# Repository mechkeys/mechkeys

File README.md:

# mechkeys

A few mechanical keyboard related kicad projects.

[103-key](http://www.keyboard-layout-editor.com/##@@=PrtSc&=Scroll%20Lock&=Pause%0ABreak&_x:1.25%3B&=Esc&_x:1%3B&=F1&=F2&=F3&=F4&_x:0.5%3B&=F5&=F6&=F7&=F8&_x:0.5%3B&=F9&=F10&=F11&=F12&_x:0.25&a:7%3B&=Home&=End%3B&@_y:0.5%3B&=Num%20Lock&=%2F%2F&=*&=-&_x:0.25&a:4%3B&=%7E%0A%60&=!%0A1&=%2F@%0A2&=%23%0A3&=$%0A4&=%25%0A5&=%5E%0A6&=%2F&%0A7&=*%0A8&=%28%0A9&=%29%0A0&=%2F_%0A-&=+%0A%2F=&_w:2%3B&=Backspace&_x:0.25&a:7%3B&=Ins&=PgUp%3B&@_f:3%3B&=7%0AHome&=8%0A%E2%86%91&=9%0APgUp&_h:2%3B&=+&_x:0.25&a:4&w:1.5%3B&=Tab&=Q&=W&=E&=R&=T&=Y&=U&=I&=O&=P&=%7B&=%7D&_w:1.5%3B&=%7C&_x:0.25%3B&=Del&=PgDn%3B&@=4%0A%E2%86%90&=5&=6%0A%E2%86%92&_x:1.25&a:4&w:1.75%3B&=Caps%20Lock&=A&=S&=D&=F&=G&=H&=J&=K&=L&=%2F:&=%22&_w:2.25%3B&=Enter%3B&@=1%0AEnd&=2%0A%E2%86%93&=3%0APgDn&_h:2%3B&=Enter&_x:0.25&a:4&w:2.25%3B&=Shift&=Z&=X&=C&=V&=B&=N&=M&=%3C&=%3E&=%3F&_w:2.75%3B&=Shift&_x:0.25%3B&=%E2%86%91%3B&@_w:2%3B&=0%0AIns&=.%0ADel&_x:1.25&a:4&w:1.25%3B&=Ctrl&_w:1.25%3B&=Win&_w:1.25%3B&=Alt&_w:6.25%3B&=&_a:4&w:1.25%3B&=Alt&_w:1.25%3B&=Win&_w:1.25%3B&=Menu&_x:0.5&a:7%3B&=%E2%86%90&=%E2%86%93&=%E2%86%92): A layout from w00dyallen in this post: [my_dream_layout_103key_99](https://www.reddit.com/r/MechanicalKeyboards/comments/4l9j7y/my_dream_layout_103key_99/)

layout.py: python script that will layout out a pcb and schematic from the output of http://www.keyboard-layout-editor.com/

dylibfix.sh: shell script that will fix the lib security errors in osx.

Apologies- I had to wipe the original and replace it. The new repo does not have most of my kicad projects. If you want a copy send me a message, but I can't keep them in the open any more.

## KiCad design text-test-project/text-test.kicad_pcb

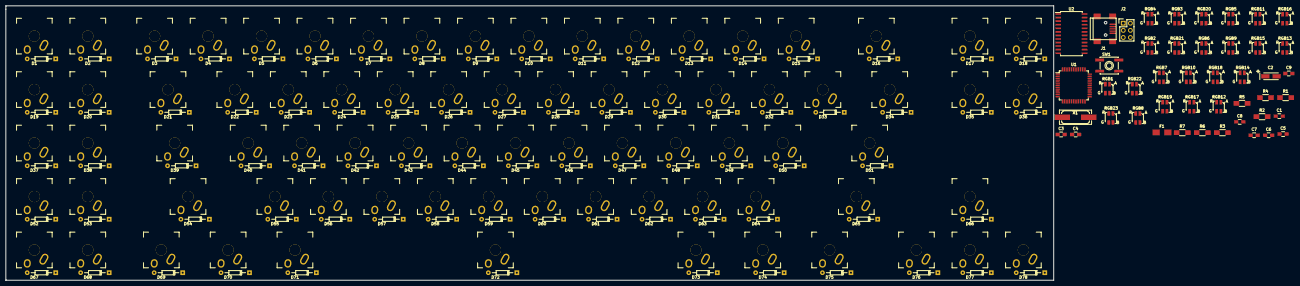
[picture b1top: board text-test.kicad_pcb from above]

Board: 2 copper layers, 373.4 x 97.8 mm, 202 parts (0 on the bottom side), 133 nets, no tracks yet.

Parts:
C1: C; C_0805_HandSoldering
C2: 10µF; TantalC_SizeA_EIA-3216_HandSoldering
C3, C4, C5, C9: 0.1µF; C_0805_HandSoldering
C6, C7: 18pF; C_0805_HandSoldering
C8: 1µF; C_0805_HandSoldering
D1, D2, D3, D4, D5, D6, D7, D8, D9, D10, D11, D12, D13, D14, D15, D16, D17, D18, D19, D20, D21, D22, D23, D24, D25, D26, D27, D28, D29, D30, D31, D32, D33, D34, D35, D36, D37, D38, D39, D40, D41, D42, D43, D44, D45, D46, D47, D48, D49, D50, D51, D52, D53, D54, D55, D56, D57, D58, D59, D60, D61, D62, D63, D64, D65, D66, D67, D68, D69, D70, D71, D72, D73, D74, D75, D76, D77, D78: D; Diode_DO-35_SOD27_Horizontal_RM10
F1: FP_Small; Fuse_SMD1206_HandSoldering
J1: USB_OTG; USB_Mini-B
J2: PRG; Pin_Header_Straight_2x03
R1: R; R_1206_HandSoldering
R2: R2; R_1206_HandSoldering
R3: R3; R_1206_HandSoldering
R4: R4; R_1206_HandSoldering
R5, R6: 22; R_1206_HandSoldering
R7: 10k; R_1206_HandSoldering
RGB1, RGB2, RGB3, RGB4, RGB5, RGB6, RGB7, RGB8, RGB9, RGB10, RGB11, RGB12, RGB13, RGB14, RGB15, RGB16, RGB17, RGB18, RGB19, RGB20, RGB21, RGB22, RGB23: Led_RGB_CA; SMP4-RGB
SW1: SW_RST; SW_SPST_EVQP0
SW_A_40: MX_LED; MXALPS-NOLED
SW_Alt_71, SW_Alt_73: MX_LED; MXALPS-NOLED
SW_B_59: MX_LED; MXALPS-NOLED
SW_Backspace_16: MX_LED; MXALPS-NOLED
SW_C_57: MX_LED; MXALPS-NOLED
SW_Caps_39: MX_LED; MXALPS-NOLED
SW_Ctrl_69: MX_LED; MXALPS-NOLED
SW_D_42: MX_LED; MXALPS-NOLED
SW_Del_35: MX_LED; MXALPS-NOLED
SW_E_24: MX_LED; MXALPS-NOLED
SW_Enter_51: MX_LED; MXALPS-NOLED
SW_F1_1, SW_F2_2, SW_F3_19, SW_F4_20, SW_F5_37, SW_F6_38, SW_F7_52, SW_F8_53, SW_F9_67, SW_F10_68: MX_LED; MXALPS-NOLED
SW_F_43: MX_LED; MXALPS-NOLED
SW_G_44: MX_LED; MXALPS-NOLED
SW_H_45: MX_LED; MXALPS-NOLED
SW_I_29: MX_LED; MXALPS-NOLED
SW_Ins_17: MX_LED; MXALPS-NOLED
SW_J_46: MX_LED; MXALPS-NOLED
SW_K_47: MX_LED; MXALPS-NOLED
SW_L_48: MX_LED; MXALPS-NOLED
SW_M_61: MX_LED; MXALPS-NOLED
SW_Menu_75: MX_LED; MXALPS-NOLED
SW_N_60: MX_LED; MXALPS-NOLED
SW_O_30: MX_LED; MXALPS-NOLED
SW_P_31: MX_LED; MXALPS-NOLED
SW_PgDn_36: MX_LED; MXALPS-NOLED
SW_PgUp_18: MX_LED; MXALPS-NOLED
SW_Q_22: MX_LED; MXALPS-NOLED
SW_R_25: MX_LED; MXALPS-NOLED
SW_S_41: MX_LED; MXALPS-NOLED
SW_Shift_54, SW_Shift_65: MX_LED; MXALPS-NOLED
SW_T_26: MX_LED; MXALPS-NOLED
SW_Tab_21: MX_LED; MXALPS-NOLED
SW_U_28: MX_LED; MXALPS-NOLED
SW_V_58: MX_LED; MXALPS-NOLED
SW_W_23: MX_LED; MXALPS-NOLED
SW_Win_70, SW_Win_74: MX_LED; MXALPS-NOLED
SW_X4Y1_3, SW_X5Y1_4, SW_X6Y1_5, SW_X7Y1_6, SW_X8Y1_7, SW_X8Y5_72, SW_X9Y1_8, SW_X10Y1_9, SW_X11Y1_10, SW_X12Y1_11, SW_X13Y1_12, SW_X13Y4_62, SW_X14Y1_13, SW_X14Y4_63, SW_X15Y1_14, SW_X15Y2_32, SW_X15Y3_49, SW_X15Y4_64, SW_X16Y1_15, SW_X16Y2_33, SW_X16Y3_50, SW_X17Y2_34, SW_X18Y5_76, SW_X19Y4_66, SW_X19Y5_77, SW_X20Y5_78: MX_LED; MXALPS-NOLED
SW_X_56: MX_LED; MXALPS-NOLED
SW_Y_27: MX_LED; MXALPS-NOLED
SW_Z_55: MX_LED; MXALPS-NOLED
U1: ATMEGA32U4RC-A; TQFP-44_10x10mm_Pitch0.8mm
U2: AN32183A; SOIC-24_7.5x15.4mm_Pitch1.27mm
X1: 16Mhz; Q_49U3HMS

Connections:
+5V: C2.1, C3.1, C4.1, C5.1, F1.2, J2.2, R7.2, RGB1.1, U1.2, U1.7, U1.14, U1.24, U1.34, U1.44
C1: SW_F1_1.SW1, SW_F3_19.SW1, SW_F5_37.SW1, SW_F7_52.SW1, SW_F9_67.SW1, SW_H_45.SW1, SW_Menu_75.SW1, SW_N_60.SW1, SW_X10Y1_9.SW1, SW_Y_27.SW1, U1.31
C2: SW_F2_2.SW1, SW_F4_20.SW1, SW_F6_38.SW1, SW_F8_53.SW1, SW_F10_68.SW1, SW_J_46.SW1, SW_M_61.SW1, SW_U_28.SW1, SW_X11Y1_10.SW1, SW_X18Y5_76.SW1, U1.32
C3: SW_Caps_39.SW1, SW_Ctrl_69.SW1, SW_I_29.SW1, SW_K_47.SW1, SW_Shift_54.SW1, SW_Tab_21.SW1, SW_X4Y1_3.SW1, SW_X12Y1_11.SW1, SW_X13Y4_62.SW1, SW_X19Y5_77.SW1
C4: SW_A_40.SW1, SW_L_48.SW1, SW_O_30.SW1, SW_Q_22.SW1, SW_Win_70.SW1, SW_X5Y1_4.SW1, SW_X13Y1_12.SW1, SW_X14Y4_63.SW1, SW_X20Y5_78.SW1, SW_Z_55.SW1
C5: SW_Alt_71.SW1, SW_Ins_17.SW1, SW_P_31.SW1, SW_S_41.SW1, SW_W_23.SW1, SW_X6Y1_5.SW1, SW_X14Y1_13.SW1, SW_X15Y3_49.SW1, SW_X15Y4_64.SW1, SW_X_56.SW1
C6: SW_C_57.SW1, SW_D_42.SW1, SW_E_24.SW1, SW_PgUp_18.SW1, SW_Shift_65.SW1, SW_X7Y1_6.SW1, SW_X8Y5_72.SW1, SW_X15Y1_14.SW1, SW_X15Y2_32.SW1, SW_X16Y3_50.SW1
C7: SW_Alt_73.SW1, SW_Del_35.SW1, SW_Enter_51.SW1, SW_F_43.SW1, SW_R_25.SW1, SW_V_58.SW1, SW_X8Y1_7.SW1, SW_X16Y1_15.SW1, SW_X16Y2_33.SW1, SW_X19Y4_66.SW1
C8: SW_B_59.SW1, SW_Backspace_16.SW1, SW_G_44.SW1, SW_PgDn_36.SW1, SW_T_26.SW1, SW_Win_74.SW1, SW_X9Y1_8.SW1, SW_X17Y2_34.SW1
D+: R6.1, U1.4
D-: R5.1, U1.3
GND: C1.2, C2.2, C3.2, C4.2, C5.2, C6.2, C7.2, C8.2, C9.2, J1.5, J1.6, J2.6, R1.2, SW1.1, U1.5, U1.15, U1.23, U1.33, U1.35, U1.43, U2.4, U2.9, U2.15, U2.23
LED_NSRT: U1.36, U2.22
LED_SCL: U1.18, U2.2
LED_SDA: U1.19, U2.3
unnamed: C1.1, U2.1, U2.13
unnamed: C6.1, U1.17, X1.1
unnamed: C7.1, U1.16, X1.2
unnamed: C8.1, U1.6
unnamed: C9.1, U1.42
unnamed: D1.2, SW_F1_1.SW2
unnamed: D2.2, SW_F2_2.SW2
unnamed: D3.2, SW_X4Y1_3.SW2
unnamed: D4.2, SW_X5Y1_4.SW2
unnamed: D5.2, SW_X6Y1_5.SW2
unnamed: D6.2, SW_X7Y1_6.SW2
unnamed: D7.2, SW_X8Y1_7.SW2
unnamed: D8.2, SW_X9Y1_8.SW2
unnamed: D9.2, SW_X10Y1_9.SW2
unnamed: D10.2, SW_X11Y1_10.SW2
unnamed: D11.2, SW_X12Y1_11.SW2
unnamed: D12.2, SW_X13Y1_12.SW2
unnamed: D13.2, SW_X14Y1_13.SW2
unnamed: D14.2, SW_X15Y1_14.SW2
unnamed: D15.2, SW_X16Y1_15.SW2
unnamed: D16.2, SW_Backspace_16.SW2
unnamed: D17.1, D18.1, D35.1, D36.1, D78.2, SW_X20Y5_78.SW2
unnamed: D17.2, SW_Ins_17.SW2
unnamed: D18.2, SW_PgUp_18.SW2
unnamed: D19.1, D20.1, D21.1, D22.1, D23.1, D24.1, D25.1, D26.1
unnamed: D19.2, SW_F3_19.SW2
unnamed: D20.2, SW_F4_20.SW2
unnamed: D21.2, SW_Tab_21.SW2
unnamed: D22.2, SW_Q_22.SW2
unnamed: D23.2, SW_W_23.SW2
unnamed: D24.2, SW_E_24.SW2
unnamed: D25.2, SW_R_25.SW2
unnamed: D26.2, SW_T_26.SW2
unnamed: D27.2, SW_Y_27.SW2
unnamed: D28.2, SW_U_28.SW2
unnamed: D29.2, SW_I_29.SW2
unnamed: D30.2, SW_O_30.SW2
unnamed: D31.2, SW_P_31.SW2
unnamed: D32.2, SW_X15Y2_32.SW2
unnamed: D33.2, SW_X16Y2_33.SW2
unnamed: D34.2, SW_X17Y2_34.SW2
unnamed: D35.2, SW_Del_35.SW2
unnamed: D36.2, SW_PgDn_36.SW2
unnamed: D37.1, D38.1, D39.1, D40.1, D41.1, D42.1, D43.1, D44.1
unnamed: D37.2, SW_F5_37.SW2
unnamed: D38.2, SW_F6_38.SW2
unnamed: D39.2, SW_Caps_39.SW2
unnamed: D40.2, SW_A_40.SW2
unnamed: D41.2, SW_S_41.SW2
unnamed: D42.2, SW_D_42.SW2
unnamed: D43.2, SW_F_43.SW2
unnamed: D44.2, SW_G_44.SW2
unnamed: D45.2, SW_H_45.SW2
unnamed: D46.2, SW_J_46.SW2
unnamed: D47.2, SW_K_47.SW2
unnamed: D48.2, SW_L_48.SW2
unnamed: D49.2, SW_X15Y3_49.SW2
unnamed: D50.2, SW_X16Y3_50.SW2
unnamed: D51.2, SW_Enter_51.SW2
unnamed: D52.1, D53.1, D54.1, D55.1, D56.1, D57.1, D58.1, D59.1
unnamed: D52.2, SW_F7_52.SW2
unnamed: D53.2, SW_F8_53.SW2
unnamed: D54.2, SW_Shift_54.SW2
unnamed: D55.2, SW_Z_55.SW2
unnamed: D56.2, SW_X_56.SW2
unnamed: D57.2, SW_C_57.SW2
unnamed: D58.2, SW_V_58.SW2
unnamed: D59.2, SW_B_59.SW2
unnamed: D60.2, SW_N_60.SW2
unnamed: D61.2, SW_M_61.SW2
unnamed: D62.2, SW_X13Y4_62.SW2
unnamed: D63.2, SW_X14Y4_63.SW2
unnamed: D64.2, SW_X15Y4_64.SW2
unnamed: D65.2, SW_Shift_65.SW2
unnamed: D66.2, SW_X19Y4_66.SW2
unnamed: D67.2, SW_F9_67.SW2
unnamed: D68.2, SW_F10_68.SW2
unnamed: D69.2, SW_Ctrl_69.SW2
unnamed: D70.2, SW_Win_70.SW2
unnamed: D71.2, SW_Alt_71.SW2
unnamed: D72.2, SW_X8Y5_72.SW2
unnamed: D73.2, SW_Alt_73.SW2
unnamed: D74.2, SW_Win_74.SW2
unnamed: D75.2, SW_Menu_75.SW2
unnamed: D76.2, SW_X18Y5_76.SW2
unnamed: D77.2, SW_X19Y5_77.SW2
unnamed: F1.1, J1.1
unnamed: J1.2, R5.2
unnamed: J1.3, R6.2
unnamed: R1.1, U2.24
unnamed: R2.1, RGB1.4
unnamed: R3.1, RGB1.3
unnamed: R4.1, RGB1.2
unnamed: U2.7, U2.17
PWM_BLUE: R2.2, U1.12
PWM_GREEN: R3.2, U1.30
PWM_RED: R4.2, U1.29
R1: D1.1, D2.1, D3.1, D4.1, D5.1, D6.1, D7.1, D8.1, U1.8
R2/SCK: J2.3, U1.9
R3/MOSI: J2.4, U1.10
R4/MISO: J2.1, U1.11
R5: D67.1, D68.1, D69.1, D70.1, D71.1, D72.1, D73.1, D74.1, U1.28
R6: D9.1, D10.1, D11.1, D12.1, D13.1, D14.1, D15.1, D16.1, U1.41
R7: D27.1, D28.1, D29.1, D30.1, D31.1, D32.1, D33.1, D34.1, U1.40
R8: D45.1, D46.1, D47.1, D48.1, D49.1, D50.1, D51.1, U1.39
R9: D60.1, D61.1, D62.1, D63.1, D64.1, D65.1, D66.1, U1.38
R10: D75.1, D76.1, D77.1, D78.1, U1.37
RST: J2.5, R7.1, SW1.2, U1.13
Z1: RGB2.3, RGB3.1, RGB5.1, RGB13.1, RGB22.3, RGB23.3, U2.19
Z2: RGB2.2, RGB3.2, RGB6.1, RGB9.2, RGB10.2, RGB11.2, RGB12.2, RGB14.1, U2.18
Z3: RGB2.1, RGB3.3, RGB7.1, RGB9.3, RGB10.3, RGB11.3, RGB12.3, RGB15.1, U2.16
Z4: RGB2.4, RGB3.4, RGB4.4, RGB8.1, RGB9.4, RGB10.4, RGB11.4, RGB12.4, RGB16.1, U2.14
Z5: RGB4.2, RGB5.2, RGB6.2, RGB7.2, RGB8.2, RGB9.1, RGB17.1, RGB20.2, RGB21.2, RGB22.2, U2.12
Z6: RGB4.3, RGB5.3, RGB6.3, RGB7.3, RGB8.3, RGB10.1, RGB18.1, RGB20.3, RGB21.3, RGB22.1, U2.11
Z7: RGB4.1, RGB5.4, RGB6.4, RGB7.4, RGB8.4, RGB19.1, RGB20.4, RGB21.4, RGB22.4, U2.10
Z8: RGB11.1, RGB13.2, RGB14.2, RGB15.2, RGB16.2, RGB17.2, RGB18.2, RGB19.2, RGB20.1, RGB23.2, U2.8
Z9: RGB12.1, RGB13.3, RGB14.3, RGB15.3, RGB16.3, RGB17.3, RGB18.3, RGB19.3, RGB21.1, RGB23.1, U2.6
Z10: RGB13.4, RGB14.4, RGB15.4, RGB16.4, RGB17.4, RGB19.4, RGB23.4, U2.5

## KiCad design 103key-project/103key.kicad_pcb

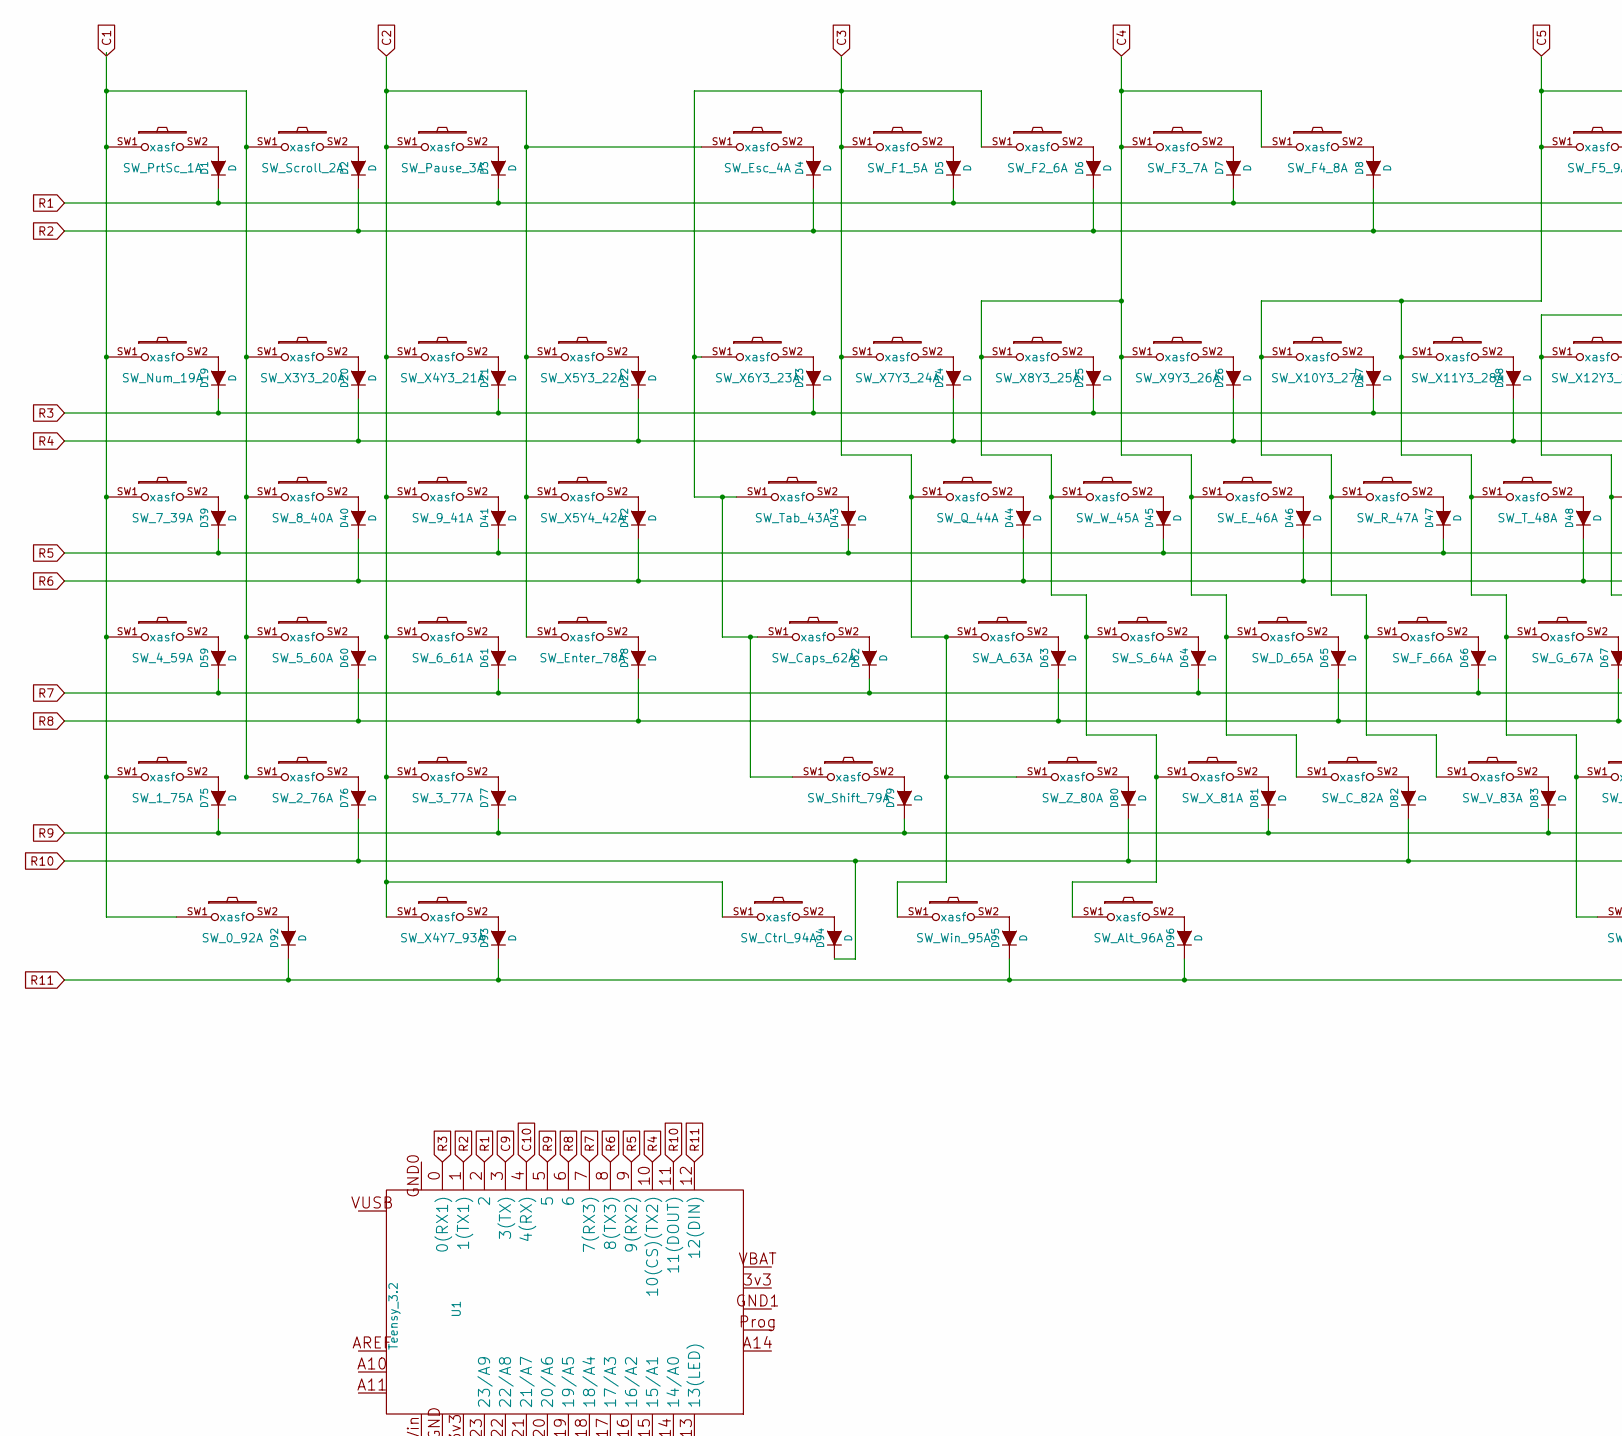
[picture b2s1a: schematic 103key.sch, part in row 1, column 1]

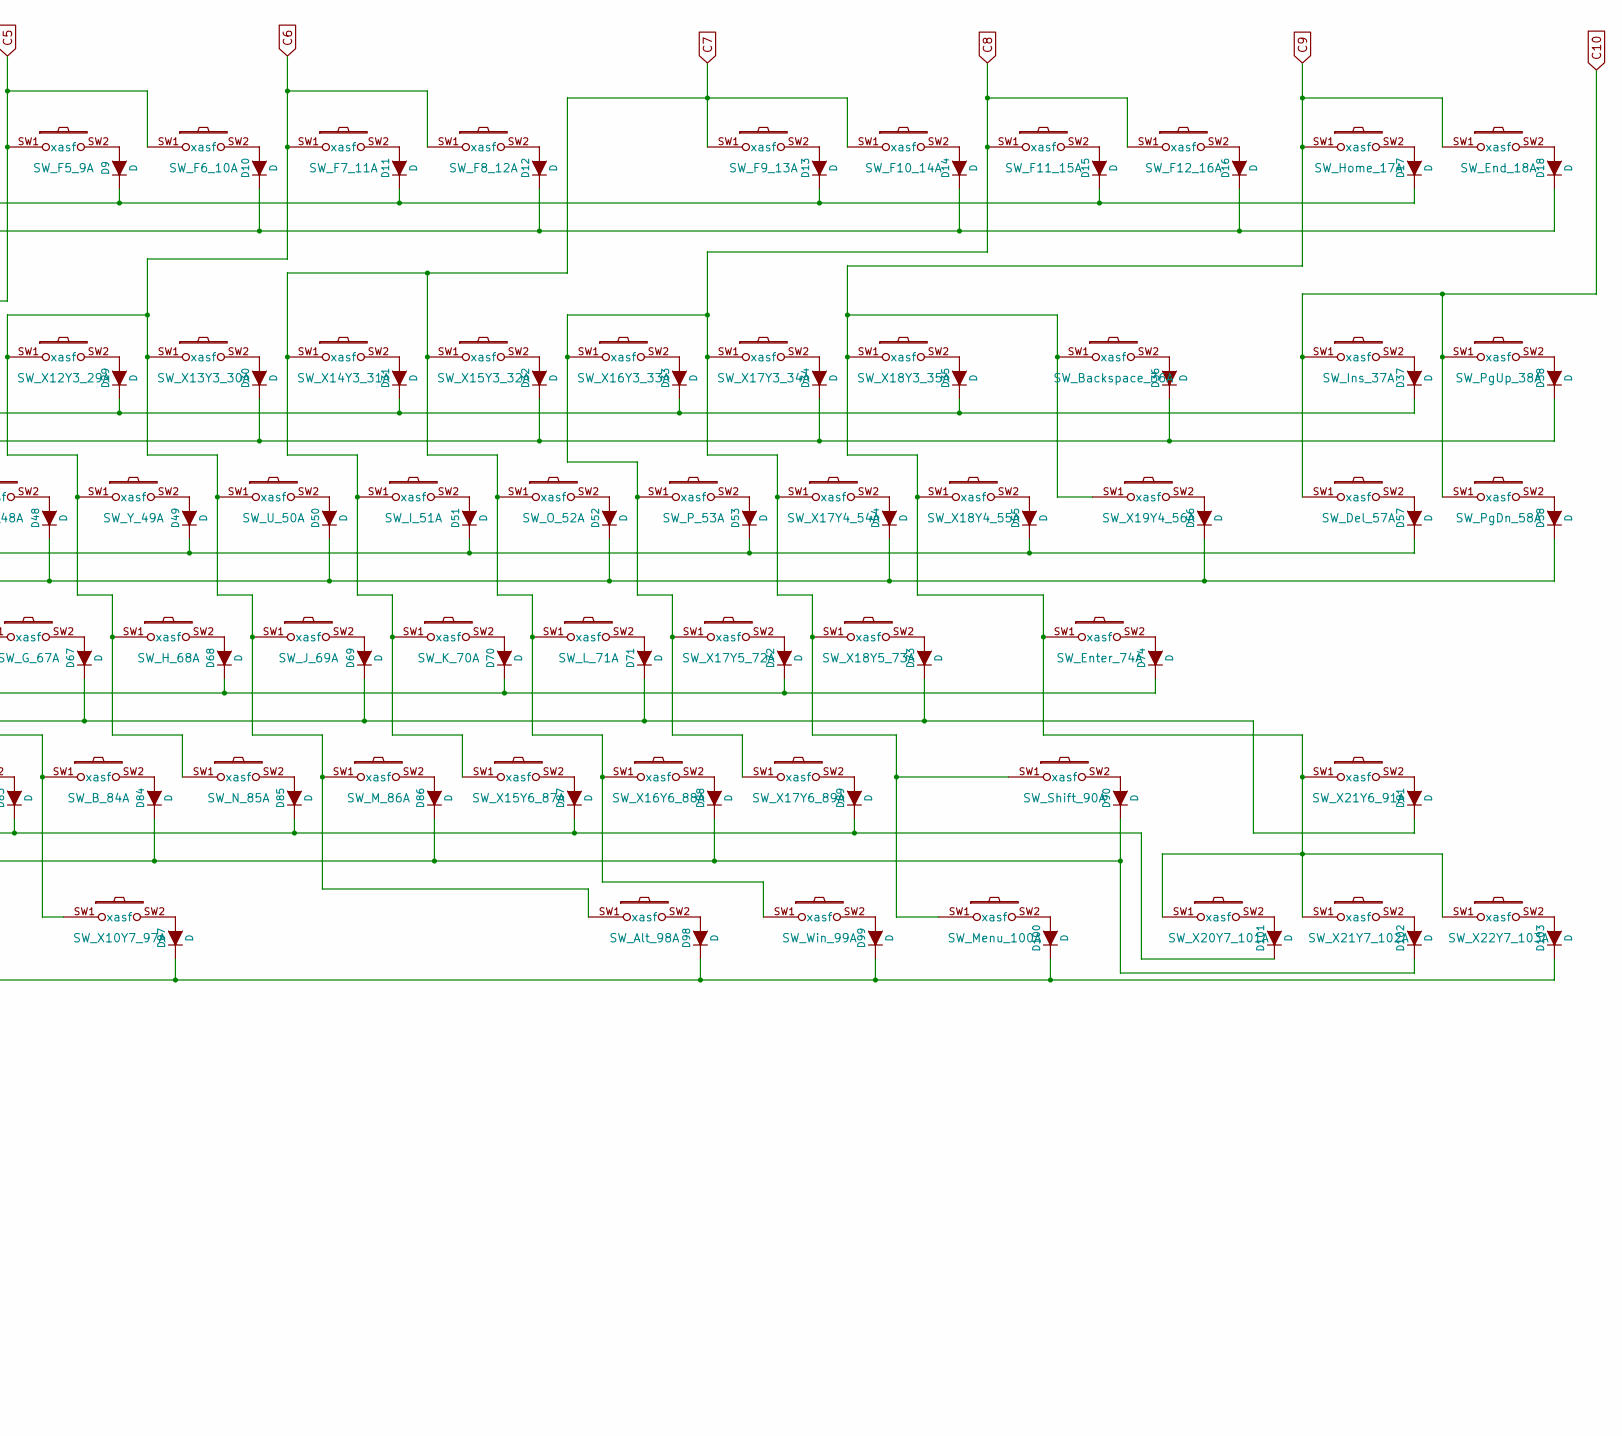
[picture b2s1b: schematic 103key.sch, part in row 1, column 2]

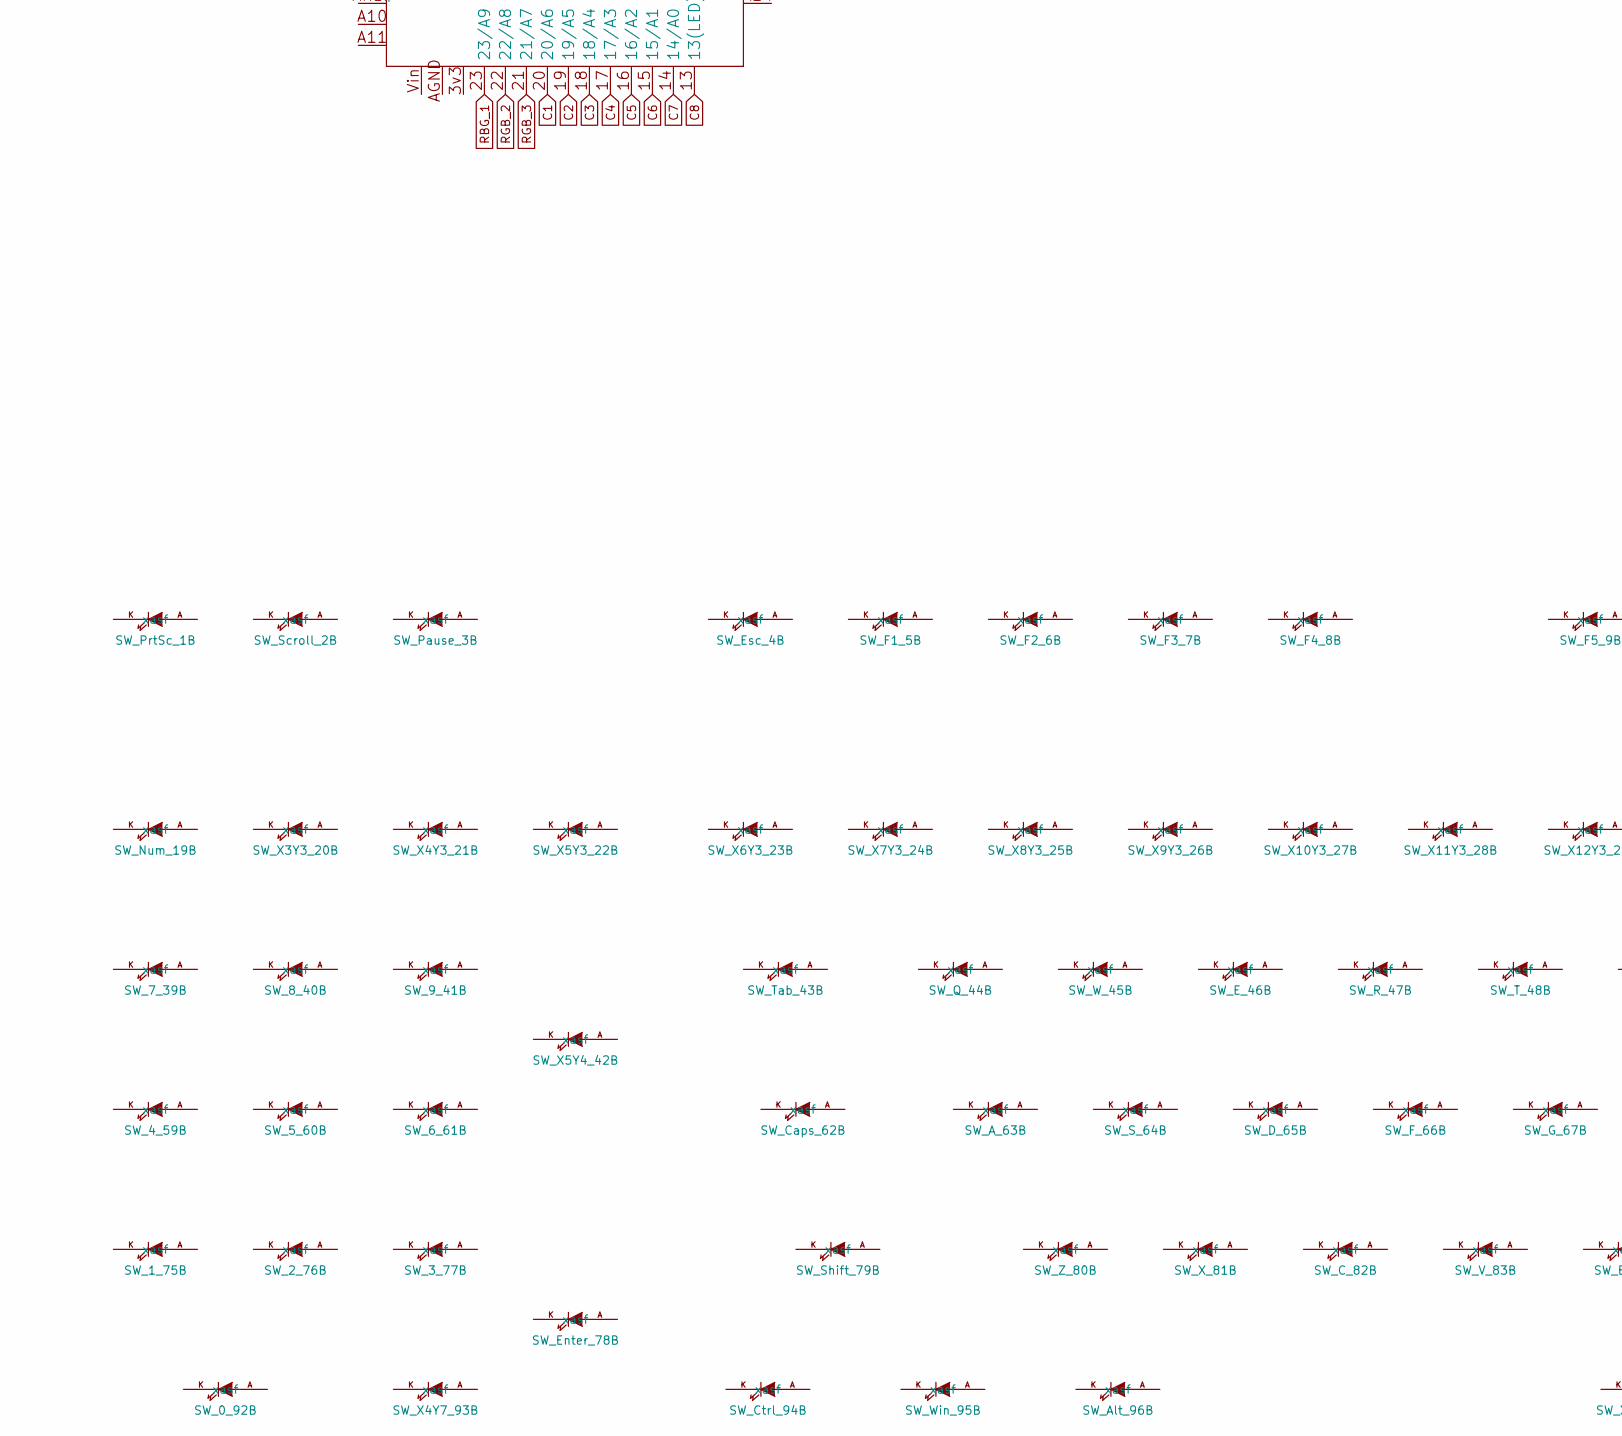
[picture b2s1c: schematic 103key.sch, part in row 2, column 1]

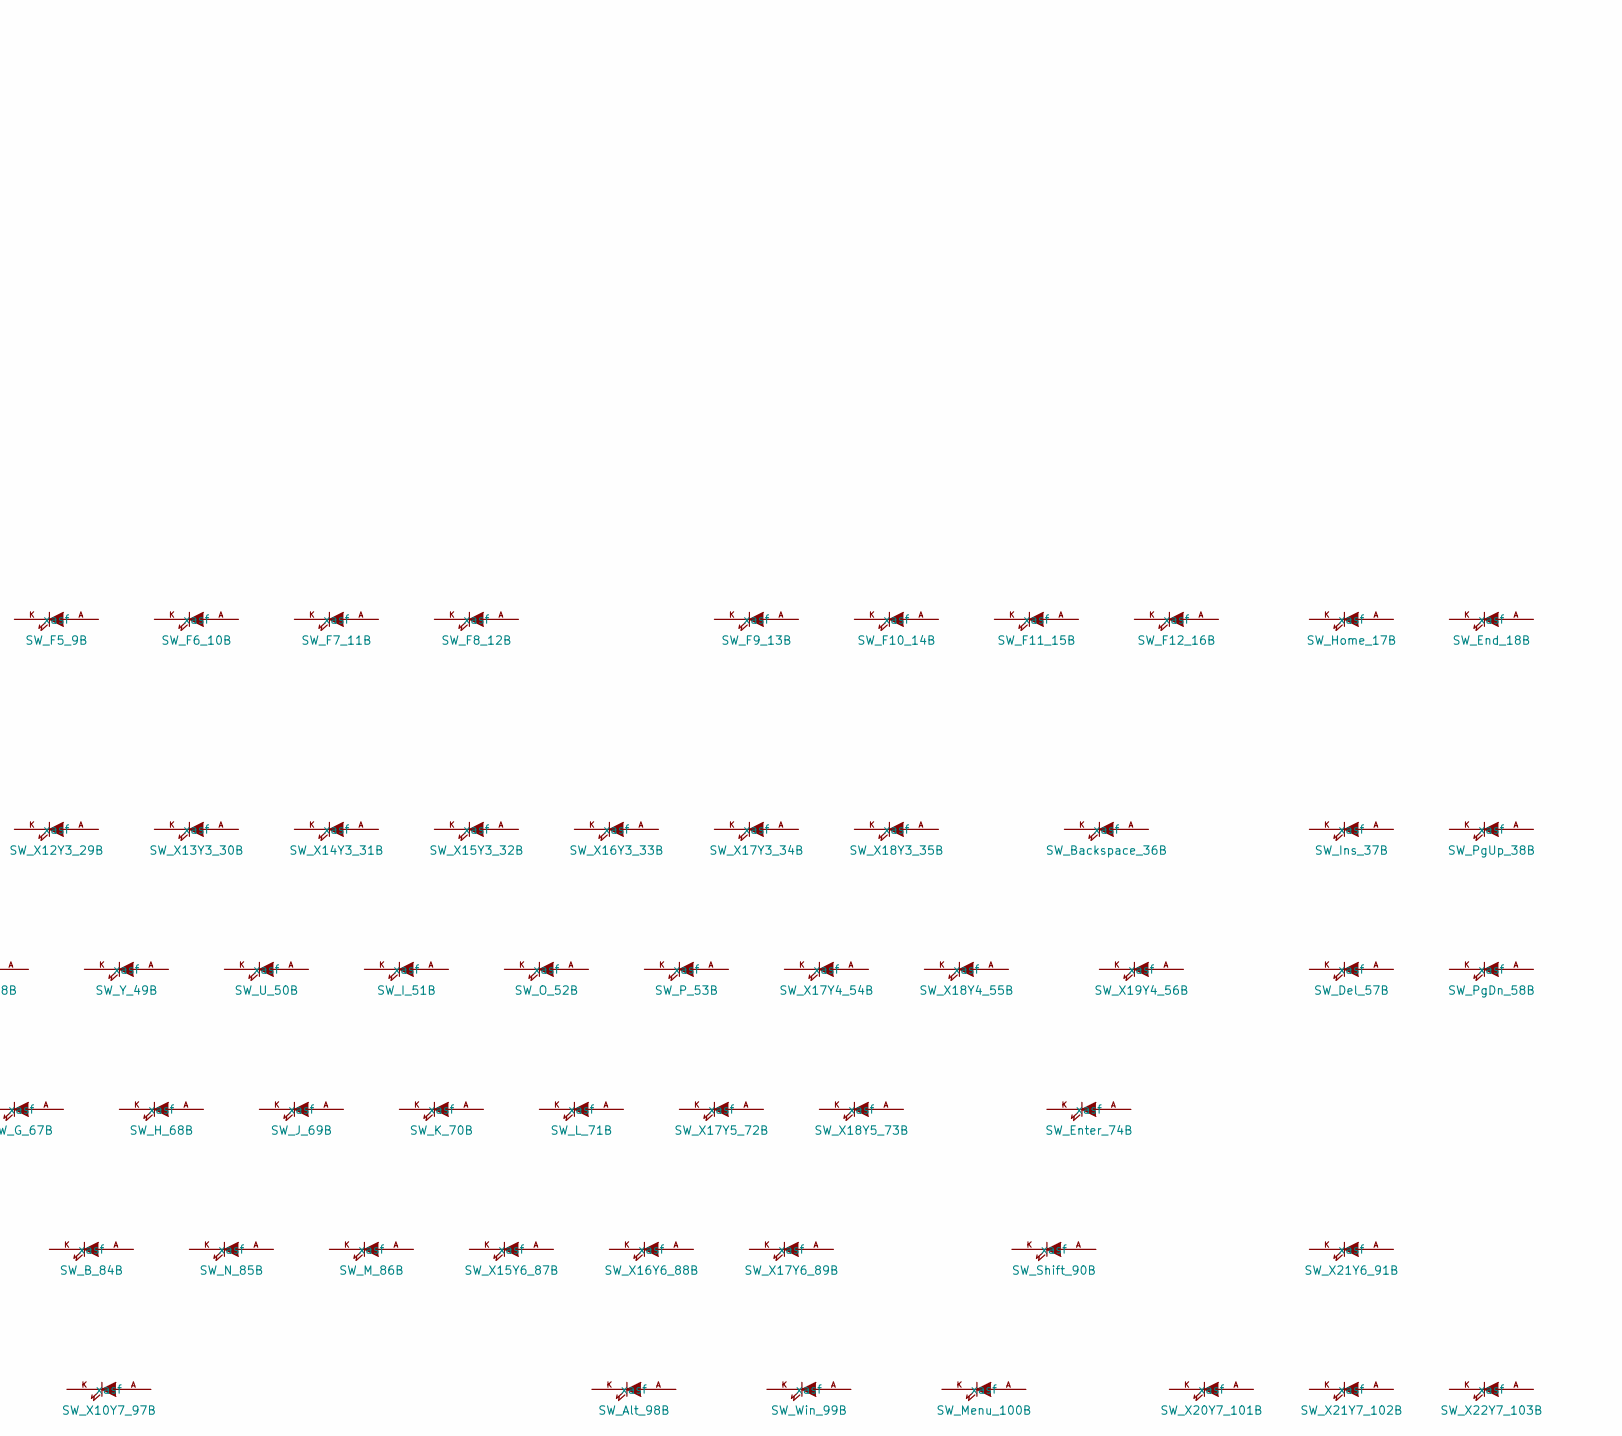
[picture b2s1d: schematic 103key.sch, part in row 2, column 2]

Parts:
D1, D2, D3, D4, D5, D6, D7, D8, D9, D10, D11, D12, D13, D14, D15, D16, D17, D18, D19, D20, D21, D22, D23, D24, D25, D26, D27, D28, D29, D30, D31, D32, D33, D34, D35, D36, D37, D38, D39, D40, D41, D42, D43, D44, D45, D46, D47, D48, D49, D50, D51, D52, D53, D54, D55, D56, D57, D58, D59, D60, D61, D62, D63, D64, D65, D66, D67, D68, D69, D70, D71, D72, D73, D74, D75, D76, D77, D78, D79, D80, D81, D82, D83, D84, D85, D86, D87, D88, D89, D90, D91, D92, D93, D94, D95, D96, D97, D98, D99, D100, D101, D102, D103: D
SW_0_92, SW_1_75, SW_2_76, SW_3_77, SW_4_59, SW_5_60, SW_6_61, SW_7_39, SW_8_40, SW_9_41: MX_LED
SW_A_63: MX_LED
SW_Alt_96, SW_Alt_98: MX_LED
SW_B_84: MX_LED
SW_Backspace_36: MX_LED
SW_C_82: MX_LED
SW_Caps_62: MX_LED
SW_Ctrl_94: MX_LED
SW_D_65: MX_LED
SW_Del_57: MX_LED
SW_E_46: MX_LED
SW_End_18: MX_LED
SW_Enter_74, SW_Enter_78: MX_LED
SW_Esc_4: MX_LED
SW_F1_5, SW_F2_6, SW_F3_7, SW_F4_8, SW_F5_9, SW_F6_10, SW_F7_11, SW_F8_12, SW_F9_13, SW_F10_14, SW_F11_15, SW_F12_16: MX_LED
SW_F_66: MX_LED
SW_G_67: MX_LED
SW_H_68: MX_LED
SW_Home_17: MX_LED
SW_I_51: MX_LED
SW_Ins_37: MX_LED
SW_J_69: MX_LED
SW_K_70: MX_LED
SW_L_71: MX_LED
SW_M_86: MX_LED
SW_Menu_100: MX_LED
SW_N_85: MX_LED
SW_Num_19: MX_LED
SW_O_52: MX_LED
SW_P_53: MX_LED
SW_Pause_3: MX_LED
SW_PgDn_58: MX_LED
SW_PgUp_38: MX_LED
SW_PrtSc_1: MX_LED
SW_Q_44: MX_LED
SW_R_47: MX_LED
SW_S_64: MX_LED
SW_Scroll_2: MX_LED
SW_Shift_79, SW_Shift_90: MX_LED
SW_T_48: MX_LED
SW_Tab_43: MX_LED
SW_U_50: MX_LED
SW_V_83: MX_LED
SW_W_45: MX_LED
SW_Win_95, SW_Win_99: MX_LED
SW_X3Y3_20, SW_X4Y3_21, SW_X4Y7_93, SW_X5Y3_22, SW_X5Y4_42, SW_X6Y3_23, SW_X7Y3_24, SW_X8Y3_25, SW_X9Y3_26, SW_X10Y3_27, SW_X10Y7_97, SW_X11Y3_28, SW_X12Y3_29, SW_X13Y3_30, SW_X14Y3_31, SW_X15Y3_32, SW_X15Y6_87, SW_X16Y3_33, SW_X16Y6_88, SW_X17Y3_34, SW_X17Y4_54, SW_X17Y5_72, SW_X17Y6_89, SW_X18Y3_35, SW_X18Y4_55, SW_X18Y5_73, SW_X19Y4_56, SW_X20Y7_101, SW_X21Y6_91, SW_X21Y7_102, SW_X22Y7_103: MX_LED
SW_X_81: MX_LED
SW_Y_49: MX_LED
SW_Z_80: MX_LED
U1: Teensy_3.2; Teensy3.2

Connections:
C1: SW_0_92.SW1, SW_1_75.SW1, SW_2_76.SW1, SW_4_59.SW1, SW_5_60.SW1, SW_7_39.SW1, SW_8_40.SW1, SW_Num_19.SW1, SW_PrtSc_1.SW1, SW_Scroll_2.SW1, SW_X3Y3_20.SW1, U1.20 (20/A6)
C2: SW_3_77.SW1, SW_6_61.SW1, SW_9_41.SW1, SW_Ctrl_94.SW1, SW_Enter_78.SW1, SW_Esc_4.SW1, SW_Pause_3.SW1, SW_X4Y3_21.SW1, SW_X4Y7_93.SW1, SW_X5Y3_22.SW1, SW_X5Y4_42.SW1, U1.19 (19/A5)
C3: SW_A_63.SW1, SW_Caps_62.SW1, SW_F1_5.SW1, SW_F2_6.SW1, SW_Q_44.SW1, SW_Shift_79.SW1, SW_Tab_43.SW1, SW_Win_95.SW1, SW_X6Y3_23.SW1, SW_X7Y3_24.SW1, SW_Z_80.SW1, U1.18 (18/A4)
C4: SW_Alt_96.SW1, SW_C_82.SW1, SW_D_65.SW1, SW_E_46.SW1, SW_F3_7.SW1, SW_F4_8.SW1, SW_S_64.SW1, SW_W_45.SW1, SW_X8Y3_25.SW1, SW_X9Y3_26.SW1, SW_X_81.SW1, U1.17 (17/A3)
C5: SW_B_84.SW1, SW_F5_9.SW1, SW_F6_10.SW1, SW_F_66.SW1, SW_G_67.SW1, SW_R_47.SW1, SW_T_48.SW1, SW_V_83.SW1, SW_X10Y3_27.SW1, SW_X10Y7_97.SW1, SW_X11Y3_28.SW1, U1.16 (16/A2)
C6: SW_Alt_98.SW1, SW_F7_11.SW1, SW_F8_12.SW1, SW_H_68.SW1, SW_J_69.SW1, SW_M_86.SW1, SW_N_85.SW1, SW_U_50.SW1, SW_X12Y3_29.SW1, SW_X13Y3_30.SW1, SW_Y_49.SW1, U1.15 (15/A1)
C7: SW_F9_13.SW1, SW_F10_14.SW1, SW_I_51.SW1, SW_K_70.SW1, SW_L_71.SW1, SW_O_52.SW1, SW_Win_99.SW1, SW_X14Y3_31.SW1, SW_X15Y3_32.SW1, SW_X15Y6_87.SW1, SW_X16Y6_88.SW1, U1.14 (14/A0)
C8: SW_F11_15.SW1, SW_F12_16.SW1, SW_Menu_100.SW1, SW_P_53.SW1, SW_Shift_90.SW1, SW_X16Y3_33.SW1, SW_X17Y3_34.SW1, SW_X17Y4_54.SW1, SW_X17Y5_72.SW1, SW_X17Y6_89.SW1, SW_X18Y5_73.SW1, U1.13 (13(LED))
C9: SW_Backspace_36.SW1, SW_End_18.SW1, SW_Enter_74.SW1, SW_Home_17.SW1, SW_X18Y3_35.SW1, SW_X18Y4_55.SW1, SW_X19Y4_56.SW1, SW_X20Y7_101.SW1, SW_X21Y6_91.SW1, SW_X21Y7_102.SW1, SW_X22Y7_103.SW1, U1.3 (3(TX))
C10: SW_Del_57.SW1, SW_Ins_37.SW1, SW_PgDn_58.SW1, SW_PgUp_38.SW1, U1.4 (4(RX))
unnamed: D1.2 (A), SW_PrtSc_1.SW2
unnamed: D2.2 (A), SW_Scroll_2.SW2
unnamed: D3.2 (A), SW_Pause_3.SW2
unnamed: D4.2 (A), SW_Esc_4.SW2
unnamed: D5.2 (A), SW_F1_5.SW2
unnamed: D6.2 (A), SW_F2_6.SW2
unnamed: D7.2 (A), SW_F3_7.SW2
unnamed: D8.2 (A), SW_F4_8.SW2
unnamed: D9.2 (A), SW_F5_9.SW2
unnamed: D10.2 (A), SW_F6_10.SW2
unnamed: D11.2 (A), SW_F7_11.SW2
unnamed: D12.2 (A), SW_F8_12.SW2
unnamed: D13.2 (A), SW_F9_13.SW2
unnamed: D14.2 (A), SW_F10_14.SW2
unnamed: D15.2 (A), SW_F11_15.SW2
unnamed: D16.2 (A), SW_F12_16.SW2
unnamed: D17.2 (A), SW_Home_17.SW2
unnamed: D18.2 (A), SW_End_18.SW2
unnamed: D19.2 (A), SW_Num_19.SW2
unnamed: D20.2 (A), SW_X3Y3_20.SW2
unnamed: D21.2 (A), SW_X4Y3_21.SW2
unnamed: D22.2 (A), SW_X5Y3_22.SW2
unnamed: D23.2 (A), SW_X6Y3_23.SW2
unnamed: D24.2 (A), SW_X7Y3_24.SW2
unnamed: D25.2 (A), SW_X8Y3_25.SW2
unnamed: D26.2 (A), SW_X9Y3_26.SW2
unnamed: D27.2 (A), SW_X10Y3_27.SW2
unnamed: D28.2 (A), SW_X11Y3_28.SW2
unnamed: D29.2 (A), SW_X12Y3_29.SW2
unnamed: D30.2 (A), SW_X13Y3_30.SW2
unnamed: D31.2 (A), SW_X14Y3_31.SW2
unnamed: D32.2 (A), SW_X15Y3_32.SW2
unnamed: D33.2 (A), SW_X16Y3_33.SW2
unnamed: D34.2 (A), SW_X17Y3_34.SW2
unnamed: D35.2 (A), SW_X18Y3_35.SW2
unnamed: D36.2 (A), SW_Backspace_36.SW2
unnamed: D37.2 (A), SW_Ins_37.SW2
unnamed: D38.2 (A), SW_PgUp_38.SW2
unnamed: D39.2 (A), SW_7_39.SW2
unnamed: D40.2 (A), SW_8_40.SW2
unnamed: D41.2 (A), SW_9_41.SW2
unnamed: D42.2 (A), SW_X5Y4_42.SW2
unnamed: D43.2 (A), SW_Tab_43.SW2
unnamed: D44.2 (A), SW_Q_44.SW2
unnamed: D45.2 (A), SW_W_45.SW2
unnamed: D46.2 (A), SW_E_46.SW2
unnamed: D47.2 (A), SW_R_47.SW2
unnamed: D48.2 (A), SW_T_48.SW2
unnamed: D49.2 (A), SW_Y_49.SW2
unnamed: D50.2 (A), SW_U_50.SW2
unnamed: D51.2 (A), SW_I_51.SW2
unnamed: D52.2 (A), SW_O_52.SW2
unnamed: D53.2 (A), SW_P_53.SW2
unnamed: D54.2 (A), SW_X17Y4_54.SW2
unnamed: D55.2 (A), SW_X18Y4_55.SW2
unnamed: D56.2 (A), SW_X19Y4_56.SW2
unnamed: D57.2 (A), SW_Del_57.SW2
unnamed: D58.2 (A), SW_PgDn_58.SW2
unnamed: D59.2 (A), SW_4_59.SW2
unnamed: D60.2 (A), SW_5_60.SW2
unnamed: D61.2 (A), SW_6_61.SW2
unnamed: D62.2 (A), SW_Caps_62.SW2
unnamed: D63.2 (A), SW_A_63.SW2
unnamed: D64.2 (A), SW_S_64.SW2
unnamed: D65.2 (A), SW_D_65.SW2
unnamed: D66.2 (A), SW_F_66.SW2
unnamed: D67.2 (A), SW_G_67.SW2
unnamed: D68.2 (A), SW_H_68.SW2
unnamed: D69.2 (A), SW_J_69.SW2
unnamed: D70.2 (A), SW_K_70.SW2
unnamed: D71.2 (A), SW_L_71.SW2
unnamed: D72.2 (A), SW_X17Y5_72.SW2
unnamed: D73.2 (A), SW_X18Y5_73.SW2
unnamed: D74.2 (A), SW_Enter_74.SW2
unnamed: D75.2 (A), SW_1_75.SW2
unnamed: D76.2 (A), SW_2_76.SW2
unnamed: D77.2 (A), SW_3_77.SW2
unnamed: D78.2 (A), SW_Enter_78.SW2
unnamed: D79.2 (A), SW_Shift_79.SW2
unnamed: D80.2 (A), SW_Z_80.SW2
unnamed: D81.2 (A), SW_X_81.SW2
unnamed: D82.2 (A), SW_C_82.SW2
unnamed: D83.2 (A), SW_V_83.SW2
unnamed: D84.2 (A), SW_B_84.SW2
unnamed: D85.2 (A), SW_N_85.SW2
unnamed: D86.2 (A), SW_M_86.SW2
unnamed: D87.2 (A), SW_X15Y6_87.SW2
unnamed: D88.2 (A), SW_X16Y6_88.SW2
unnamed: D89.2 (A), SW_X17Y6_89.SW2
unnamed: D90.2 (A), SW_Shift_90.SW2
unnamed: D91.2 (A), SW_X21Y6_91.SW2
unnamed: D92.2 (A), SW_0_92.SW2
unnamed: D93.2 (A), SW_X4Y7_93.SW2
unnamed: D94.2 (A), SW_Ctrl_94.SW2
unnamed: D95.2 (A), SW_Win_95.SW2
unnamed: D96.2 (A), SW_Alt_96.SW2
unnamed: D97.2 (A), SW_X10Y7_97.SW2
unnamed: D98.2 (A), SW_Alt_98.SW2
unnamed: D99.2 (A), SW_Win_99.SW2
unnamed: D100.2 (A), SW_Menu_100.SW2
unnamed: D101.2 (A), SW_X20Y7_101.SW2
unnamed: D102.2 (A), SW_X21Y7_102.SW2
unnamed: D103.2 (A), SW_X22Y7_103.SW2
R1: D1.1 (K), D3.1 (K), D5.1 (K), D7.1 (K), D9.1 (K), D11.1 (K), D13.1 (K), D15.1 (K), D17.1 (K), U1.2
R2: D2.1 (K), D4.1 (K), D6.1 (K), D8.1 (K), D10.1 (K), D12.1 (K), D14.1 (K), D16.1 (K), D18.1 (K), U1.1 (1(TX1))
R3: D19.1 (K), D21.1 (K), D23.1 (K), D25.1 (K), D27.1 (K), D29.1 (K), D31.1 (K), D33.1 (K), D35.1 (K), D37.1 (K), U1.0 (0(RX1))
R4: D20.1 (K), D22.1 (K), D24.1 (K), D26.1 (K), D28.1 (K), D30.1 (K), D32.1 (K), D34.1 (K), D36.1 (K), D38.1 (K), U1.10 (10(CS)(TX2))
R5: D39.1 (K), D41.1 (K), D43.1 (K), D45.1 (K), D47.1 (K), D49.1 (K), D51.1 (K), D53.1 (K), D55.1 (K), D57.1 (K), U1.9 (9(RX2))
R6: D40.1 (K), D42.1 (K), D44.1 (K), D46.1 (K), D48.1 (K), D50.1 (K), D52.1 (K), D54.1 (K), D56.1 (K), D58.1 (K), U1.8 (8(TX3))
R7: D59.1 (K), D61.1 (K), D62.1 (K), D64.1 (K), D66.1 (K), D68.1 (K), D70.1 (K), D72.1 (K), D74.1 (K), U1.7 (7(RX3))
R8: D60.1 (K), D63.1 (K), D65.1 (K), D67.1 (K), D69.1 (K), D71.1 (K), D73.1 (K), D78.1 (K), D91.1 (K), U1.6
R9: D75.1 (K), D77.1 (K), D79.1 (K), D81.1 (K), D83.1 (K), D85.1 (K), D87.1 (K), D89.1 (K), D101.1 (K), U1.5
R10: D76.1 (K), D80.1 (K), D82.1 (K), D84.1 (K), D86.1 (K), D88.1 (K), D90.1 (K), D94.1 (K), D102.1 (K), U1.11 (11(DOUT))
R11: D92.1 (K), D93.1 (K), D95.1 (K), D96.1 (K), D97.1 (K), D98.1 (K), D99.1 (K), D100.1 (K), D103.1 (K), U1.12 (12(DIN))

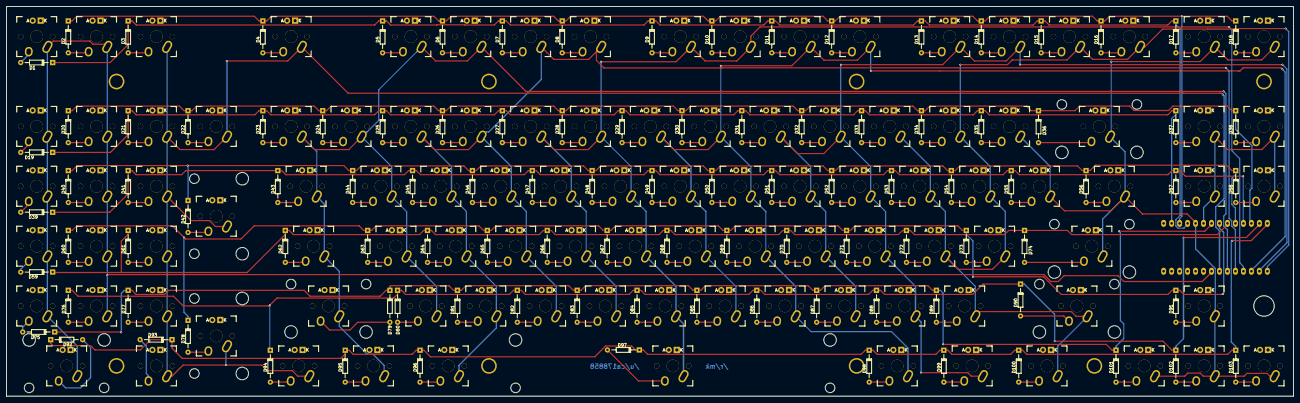
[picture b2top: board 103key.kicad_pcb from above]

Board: 2 copper layers, 409.5 x 124.0 mm, 215 parts (1 on the bottom side), 124 nets.

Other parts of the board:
CHERRY: MX; CHERRY_PCB_225H_STABILIZER
CHERRY#2: MX; CHERRY_PCB_275H_STABILIZER
CHERRY#3, CHERRY#4: MX; CHERRY_PCB_200H_STABILIZER
CHERRY#5: MX; CHERRY_PCB_225H_STABILIZER
CHERRY#6: MX; CHERRY_PCB_625H_STABILIZER
STA: Stabilizer; CHERRY_PCB_200_STABILIZER
STA#2: Stabilizer; CHERRY_PCB_200_STABILIZER
